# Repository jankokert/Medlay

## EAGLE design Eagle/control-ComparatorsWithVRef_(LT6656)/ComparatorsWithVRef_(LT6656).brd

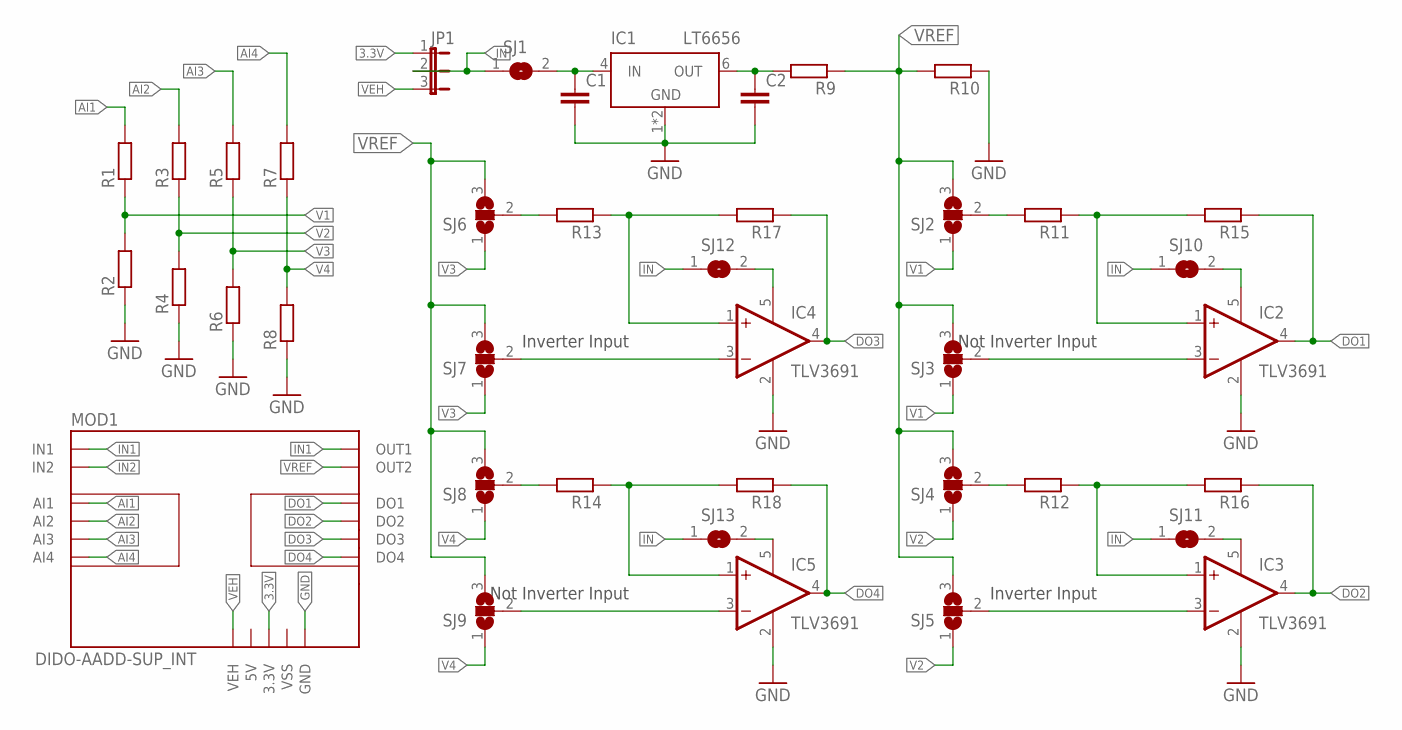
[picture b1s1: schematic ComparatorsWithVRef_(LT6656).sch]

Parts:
C1: 0.1u; C0805
C2: 1u; C0805
IC1: LT6656; TSOT23-6
IC2, IC3, IC4, IC5: TLV3691; DCK
JP1: JP2E; JP2
MOD1: DIDO-AADD-SUP_INT; DIDO-AADD-SUP
R1, R2, R3, R4, R5, R6, R7, R8, R9, R10, R11, R12, R13, R14, R15, R16, R17, R18: R-EU_R0805; R0805
SJ1, SJ10, SJ11, SJ12, SJ13: SJ
SJ2, SJ3, SJ4, SJ5, SJ6, SJ7, SJ8, SJ9: SJ3

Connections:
3.3V: JP1.1, MOD1.3.3V
5V: MOD1.5V
AI1: MOD1.AI1, R1.2
AI2: MOD1.AI2, R3.2
AI3: MOD1.AI3, R5.2
AI4: MOD1.AI4, R7.2
DO1: IC2.4 (OUT), MOD1.DO1, R15.1
DO2: IC3.4 (OUT), MOD1.DO2, R16.1
DO3: IC4.4 (OUT), MOD1.DO3, R17.1
DO4: IC5.4 (OUT), MOD1.DO4, R18.1
GND: C1.2, C2.2, IC1.1 (GND), IC1.2 (GND), IC2.2 (V-), IC3.2 (V-), IC4.2 (V-), IC5.2 (V-), MOD1.GND1 (GND), MOD1.GND2 (GND), MOD1.GND3 (GND), MOD1.GND4 (GND), R2.1, R4.1, R6.1, R8.1, R10.1
IN: JP1.2, SJ1.1, SJ10.1, SJ11.1, SJ12.1, SJ13.1
IN1: MOD1.IN1, MOD1.IN2 (IN1), MOD1.IN3 (IN1), MOD1.IN4 (IN1), MOD1.OUT1, MOD1.OUT2 (OUT1), MOD1.OUT3 (OUT1), MOD1.OUT4 (OUT1)
IN2: MOD1.IN2_1 (IN2), MOD1.IN2_2 (IN2), MOD1.IN2_3 (IN2), MOD1.IN2_4 (IN2)
unnamed: IC3.1 (+IN), R12.1, R16.2
unnamed: IC2.3 (-IN), SJ3.2
unnamed: R12.2, SJ4.2
unnamed: C2.1, IC1.6 (OUT), R9.2
unnamed: IC2.1 (+IN), R11.1, R15.2
unnamed: R11.2, SJ2.2
unnamed: IC3.3 (-IN), SJ5.2
unnamed: R13.2, SJ6.2
unnamed: IC4.3 (-IN), SJ7.2
unnamed: R14.2, SJ8.2
unnamed: IC2.5 (V+), SJ10.2
unnamed: IC4.1 (+IN), R13.1, R17.2
unnamed: IC5.3 (-IN), SJ9.2
unnamed: IC5.1 (+IN), R14.1, R18.2
unnamed: IC5.5 (V+), SJ13.2
unnamed: IC4.5 (V+), SJ12.2
unnamed: IC3.5 (V+), SJ11.2
unnamed: C1.1, IC1.4 (IN), SJ1.2
V1: R1.1, R2.2, SJ2.1, SJ3.1
V2: R3.1, R4.2, SJ4.1, SJ5.1
V3: R5.1, R6.2, SJ6.1, SJ7.1
V4: R7.1, R8.2, SJ8.1, SJ9.1
VEH: JP1.3, MOD1.VEH
VREF: MOD1.OUT2_1 (OUT2), MOD1.OUT2_2 (OUT2), MOD1.OUT2_3 (OUT2), MOD1.OUT2_4 (OUT2), R9.1, R10.2, SJ2.3, SJ3.3, SJ4.3, SJ5.3, SJ6.3, SJ7.3, SJ8.3, SJ9.3
VSS: MOD1.VSS

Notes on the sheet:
Not Inverter Input
Inverter Input

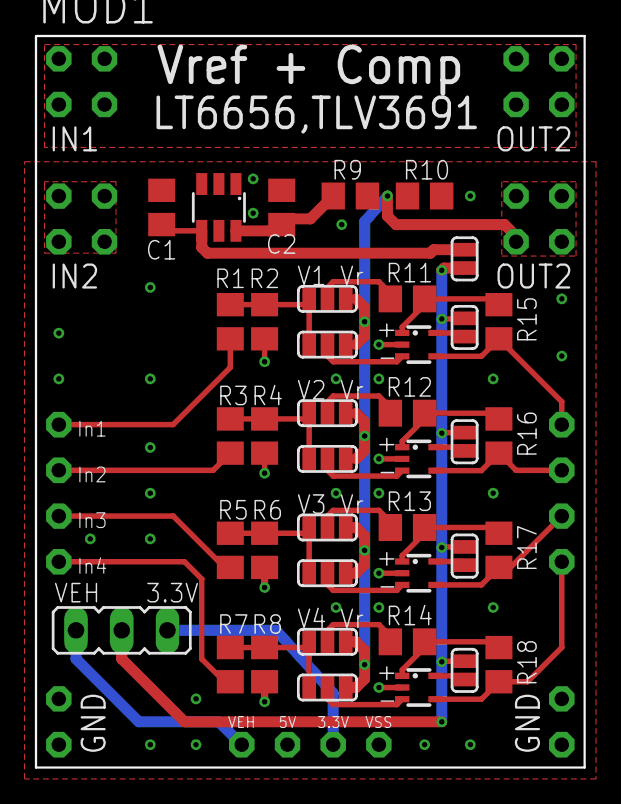
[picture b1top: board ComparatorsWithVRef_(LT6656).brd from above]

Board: 2 copper layers, 30.5 x 40.6 mm, 40 parts (0 on the bottom side), 37 nets.

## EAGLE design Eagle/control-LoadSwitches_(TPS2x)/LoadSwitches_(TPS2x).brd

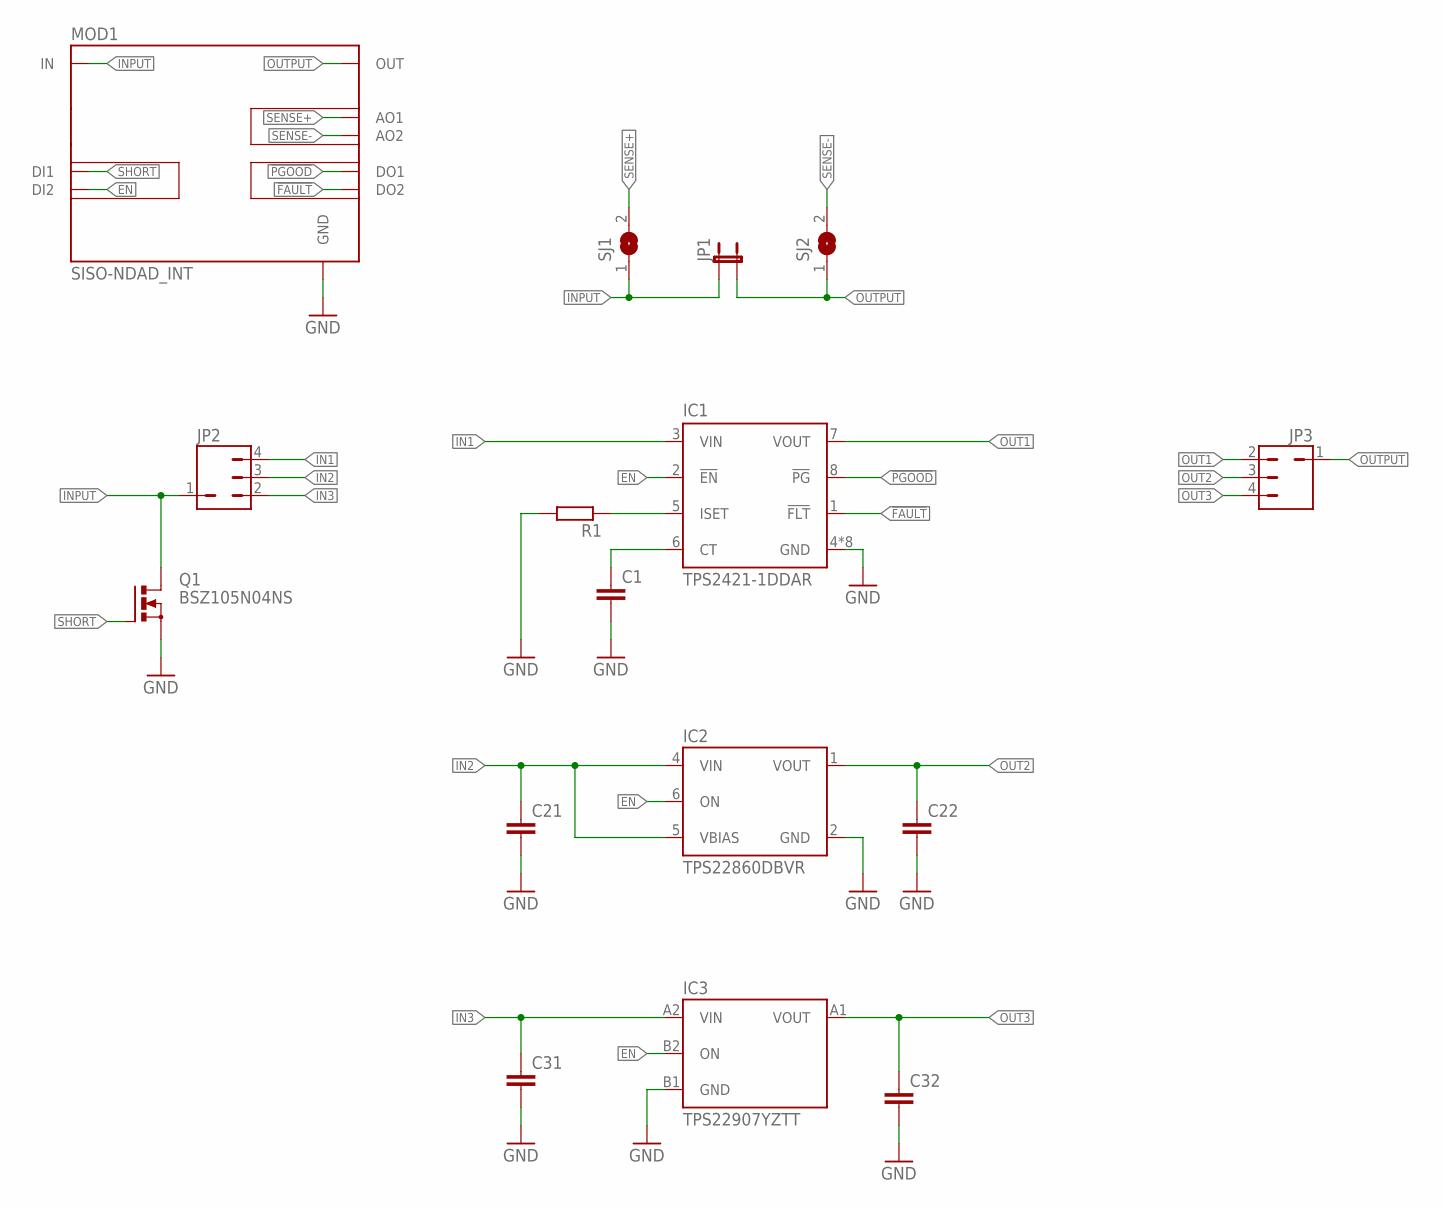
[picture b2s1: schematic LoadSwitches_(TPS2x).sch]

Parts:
C1, C21, C22, C31, C32: C-EUC0805; C0805
IC1: TPS2421-1DDAR; HSOP8
IC2: TPS22860DBVR; SOT23-6
IC3: TPS22907YZTT; BGA4C50P2X2_90X90X63
JP1: JP2_SMALL_PAD
JP2, JP3: JP3Q; JP1-3
MOD1: SISO-NDAD_INT; SISO-NDAD
Q1: BSZ105N04NS; PG-TDSON-8
R1: R-EU_R0805; R0805
SJ1, SJ2: SJ2

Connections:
!FAULT: IC1.1 (!FLT), MOD1.DO2
!PGOOD: IC1.8 (!PG), MOD1.DO1
EN: IC1.2 (!EN), IC2.6 (ON), IC3.B2 (ON), MOD1.DI2
GND: C1.2, C21.2, C22.2, C31.2, C32.2, IC1.4 (GND), IC1.EXP (GND), IC1.P$1 (GND), IC1.P$2 (GND), IC1.P$3 (GND), IC1.P$4 (GND), IC1.P$5 (GND), IC1.P$6 (GND), IC2.2 (GND), IC3.B1 (GND), MOD1.GND1 (GND), MOD1.GND2 (GND), MOD1.GND3 (GND), MOD1.GND4 (GND), Q1.1 (S), Q1.2 (S), Q1.3 (S), R1.2
IN1: IC1.3 (VIN), JP2.4
IN2: C21.1, IC2.4 (VIN), IC2.5 (VBIAS), JP2.3
IN3: C31.1, IC3.A2 (VIN), JP2.2
INPUT: JP1.1, JP2.1, MOD1.IN1 (IN), MOD1.IN2 (IN), MOD1.IN3 (IN), MOD1.IN4 (IN), Q1.5 (D), Q1.6 (D), Q1.7 (D), Q1.8 (D), Q1.TH (D), SJ1.1
unnamed: IC1.5 (ISET), R1.1
unnamed: C1.1, IC1.6 (CT)
OUT1: IC1.7 (VOUT), JP3.2
OUT2: C22.1, IC2.1 (VOUT), JP3.3
OUT3: C32.1, IC3.A1 (VOUT), JP3.4
OUTPUT: JP1.2, JP3.1, MOD1.OUT1_1 (OUT), MOD1.OUT1_2 (OUT), MOD1.OUT1_3 (OUT), MOD1.OUT1_4 (OUT), SJ2.1
SENSE+: MOD1.AO1, SJ1.2
SENSE-: MOD1.AO2, SJ2.2
SHORT: MOD1.DI1, Q1.4 (G)

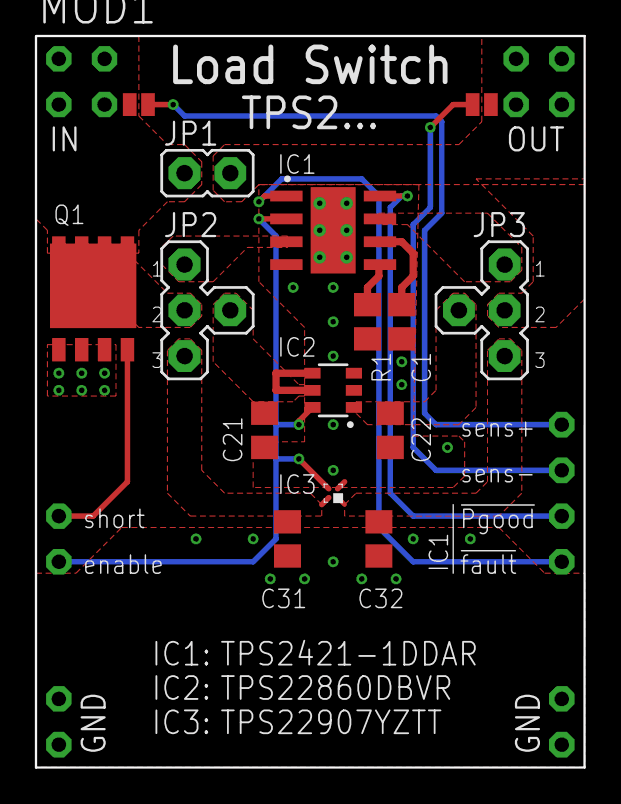
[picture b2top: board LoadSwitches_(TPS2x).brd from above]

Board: 2 copper layers, 30.5 x 40.6 mm, 16 parts (0 on the bottom side), 17 nets.

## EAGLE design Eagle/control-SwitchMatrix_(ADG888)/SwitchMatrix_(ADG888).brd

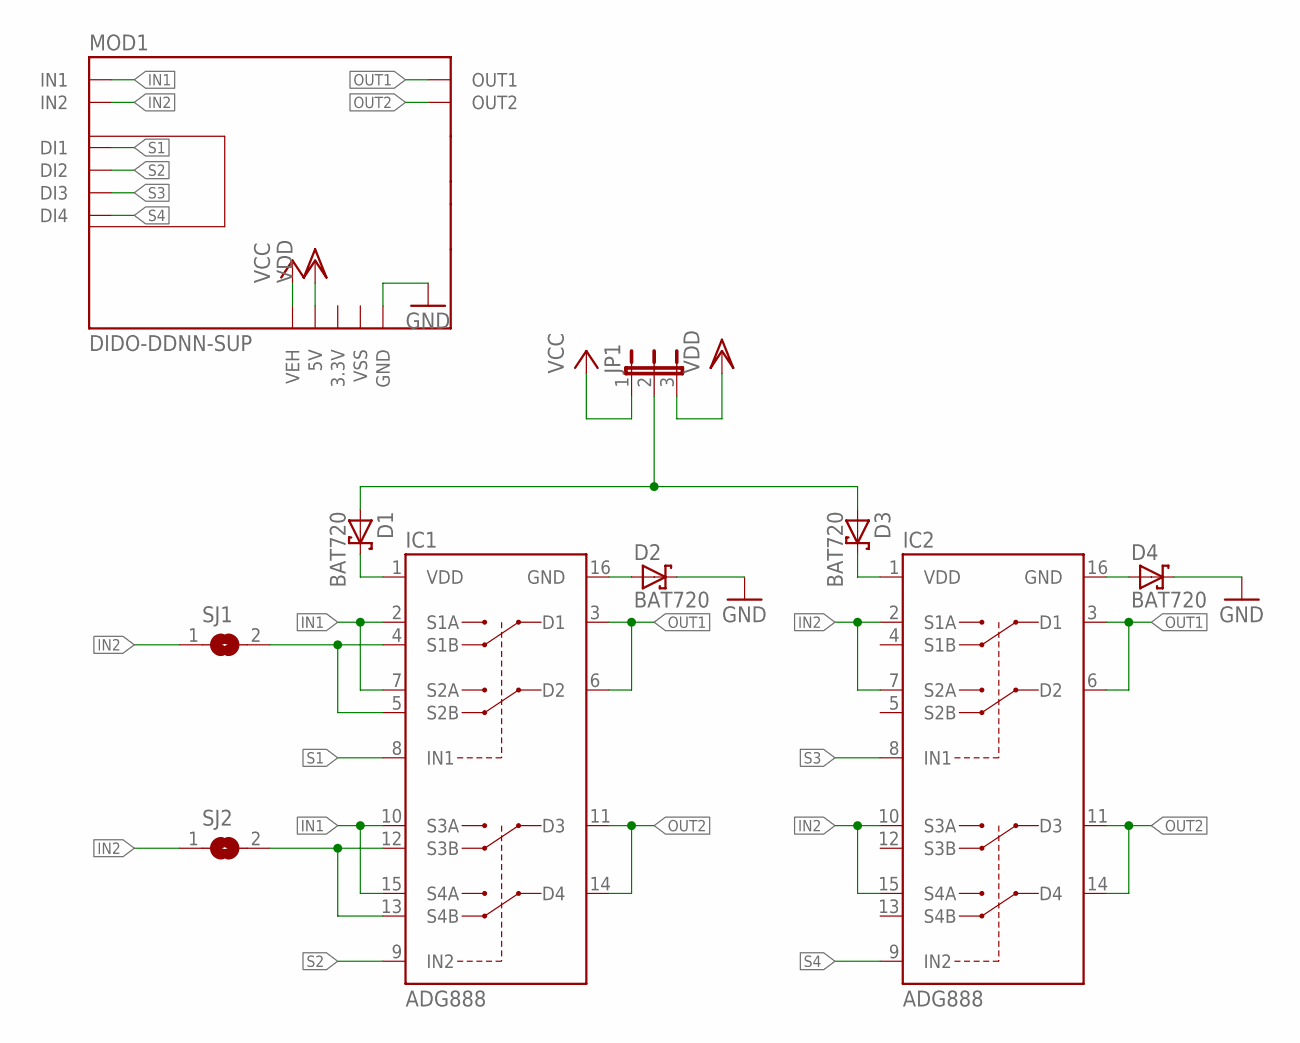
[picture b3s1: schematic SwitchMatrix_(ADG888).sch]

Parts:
D1, D2, D3, D4: BAT720; SOT23
IC1, IC2: ADG888; TSSOP16
JP1: JP2E; JP2
MOD1: DIDO-DDNN-SUP
SJ1, SJ2: SJ

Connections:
3.3V: MOD1.3.3V
GND: D2.3 (C), D4.3 (C), MOD1.GND1 (GND), MOD1.GND2 (GND), MOD1.GND3 (GND), MOD1.GND4 (GND)
IN1: IC1.2 (S1A), IC1.7 (S2A), IC1.10 (S3A), IC1.15 (S4A), MOD1.IN1_1 (IN1), MOD1.IN1_2 (IN1), MOD1.IN1_3 (IN1), MOD1.IN1_4 (IN1)
IN2: IC2.2 (S1A), IC2.7 (S2A), IC2.10 (S3A), IC2.15 (S4A), MOD1.IN2_1 (IN2), MOD1.IN2_2 (IN2), MOD1.IN2_3 (IN2), MOD1.IN2_4 (IN2), SJ1.1, SJ2.1
unnamed: IC1.4 (S1B), IC1.5 (S2B), SJ1.2
unnamed: IC1.12 (S3B), IC1.13 (S4B), SJ2.2
unnamed: D2.1 (A), IC1.16 (GND)
unnamed: D1.3 (C), IC1.1 (VDD)
unnamed: D3.3 (C), IC2.1 (VDD)
unnamed: D4.1 (A), IC2.16 (GND)
unnamed: D1.1 (A), D3.1 (A), JP1.2
OUT1: IC1.3 (D1), IC1.6 (D2), IC2.3 (D1), IC2.6 (D2), MOD1.OUT1_1 (OUT1), MOD1.OUT1_2 (OUT1), MOD1.OUT1_3 (OUT1), MOD1.OUT1_4 (OUT1)
OUT2: IC1.11 (D3), IC1.14 (D4), IC2.11 (D3), IC2.14 (D4), MOD1.OUT2_1 (OUT2), MOD1.OUT2_2 (OUT2), MOD1.OUT2_3 (OUT2), MOD1.OUT2_4 (OUT2)
S1: IC1.8 (IN1), MOD1.DI1
S2: IC1.9 (IN2), MOD1.DI2
S3: IC2.8 (IN1), MOD1.DI3
S4: IC2.9 (IN2), MOD1.DI4
VCC: JP1.1, MOD1.VEH
VDD: JP1.3, MOD1.5V
VSS: MOD1.VSS

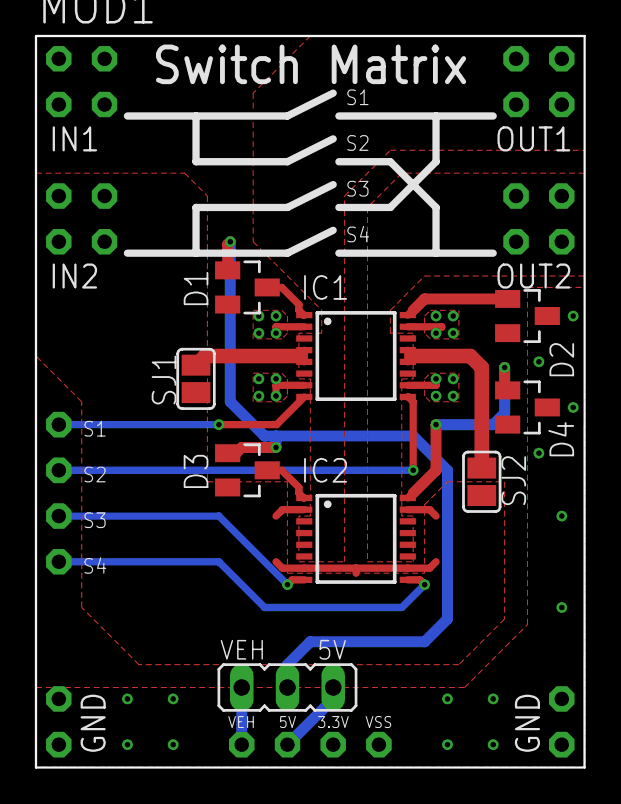
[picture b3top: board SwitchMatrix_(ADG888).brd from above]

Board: 2 copper layers, 30.5 x 40.6 mm, 10 parts (0 on the bottom side), 18 nets.

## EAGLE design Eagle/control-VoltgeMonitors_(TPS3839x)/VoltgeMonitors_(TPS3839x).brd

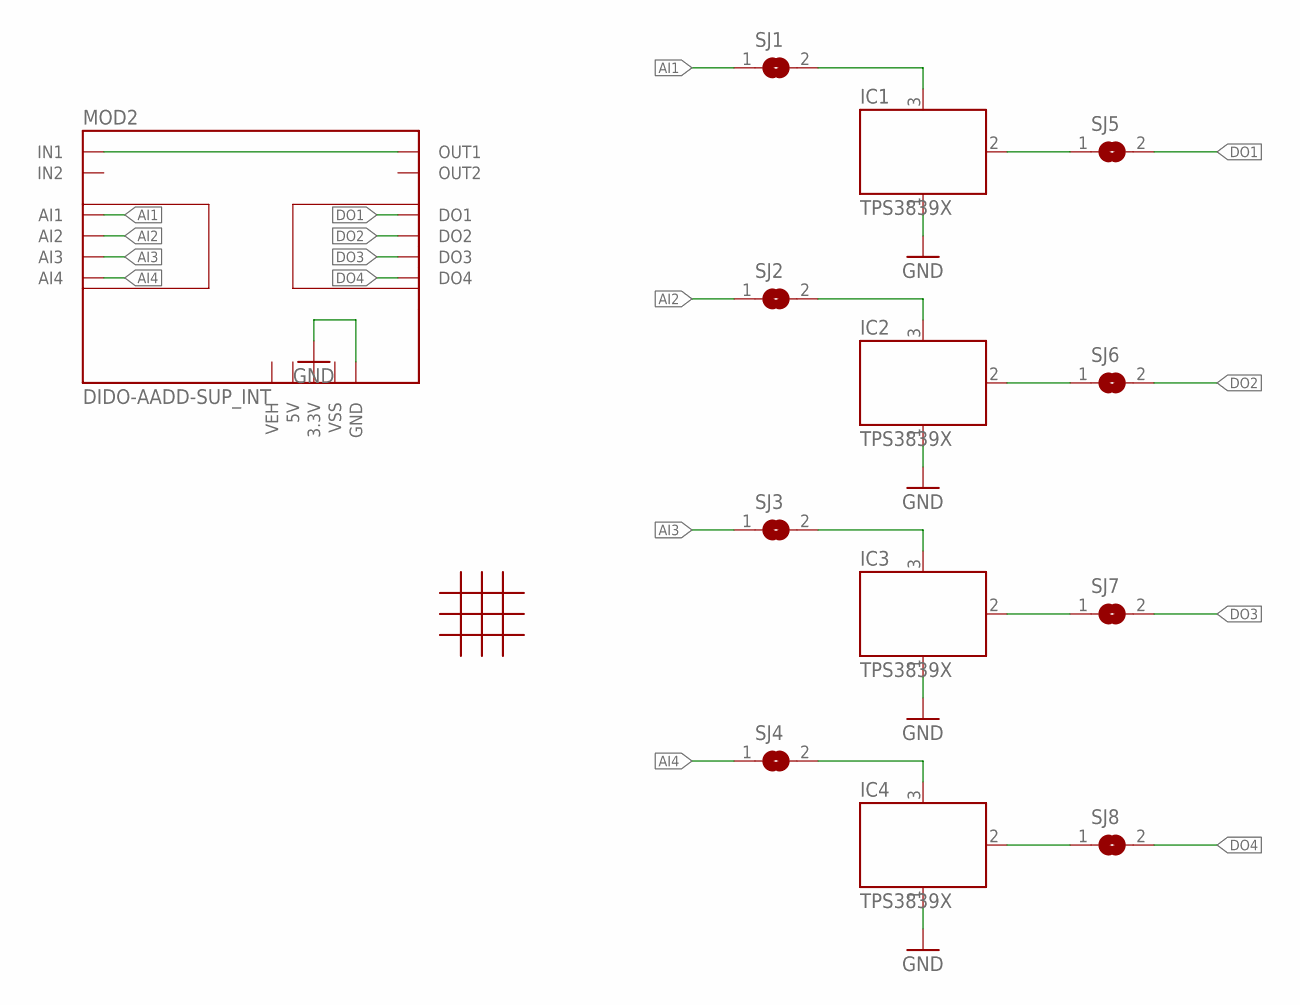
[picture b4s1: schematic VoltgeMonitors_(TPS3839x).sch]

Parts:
IC1, IC2, IC3, IC4: TPS3839X; DBZ_R-PDSO-G3
MOD2: DIDO-AADD-SUP_INT; DIDO-AADD-SUP
SJ1, SJ2, SJ3, SJ4, SJ5, SJ6, SJ7, SJ8: SJ2
U$1: SMD; SMD-PROTOTYPE

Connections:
3.3V: MOD2.3.3V
5V: MOD2.5V
AI1: MOD2.AI1, SJ1.1
AI2: MOD2.AI2, SJ2.1
AI3: MOD2.AI3, SJ3.1
AI4: MOD2.AI4, SJ4.1
DO1: MOD2.DO1, SJ5.2
DO2: MOD2.DO2, SJ6.2
DO3: MOD2.DO3, SJ7.2
DO4: MOD2.DO4, SJ8.2
GND: IC1.1 (GND), IC2.1 (GND), IC3.1 (GND), IC4.1 (GND), MOD2.GND1 (GND), MOD2.GND2 (GND), MOD2.GND3 (GND), MOD2.GND4 (GND)
IN: MOD2.IN1, MOD2.IN2 (IN1), MOD2.IN3 (IN1), MOD2.IN4 (IN1), MOD2.OUT1, MOD2.OUT2 (OUT1), MOD2.OUT3 (OUT1), MOD2.OUT4 (OUT1)
unnamed: IC1.3 (VDD), SJ1.2
unnamed: IC2.3 (VDD), SJ2.2
unnamed: IC3.3 (VDD), SJ3.2
unnamed: IC4.3 (VDD), SJ4.2
unnamed: IC4.2 (/RST), SJ8.1
unnamed: IC3.2 (/RST), SJ7.1
unnamed: IC2.2 (/RST), SJ6.1
unnamed: IC1.2 (/RST), SJ5.1
VEH: MOD2.VEH
VSS: MOD2.VSS

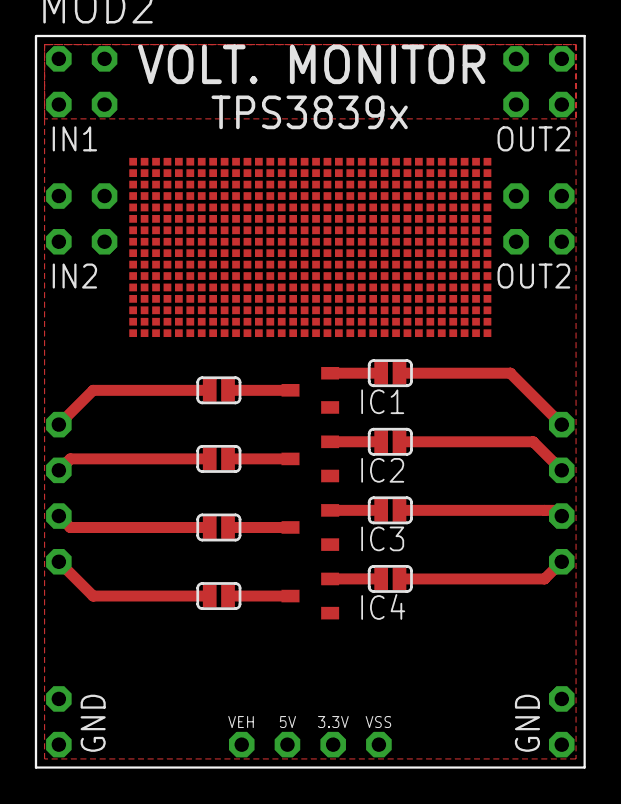
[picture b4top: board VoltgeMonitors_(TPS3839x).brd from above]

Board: 2 copper layers, 30.5 x 40.6 mm, 14 parts (0 on the bottom side), 18 nets.

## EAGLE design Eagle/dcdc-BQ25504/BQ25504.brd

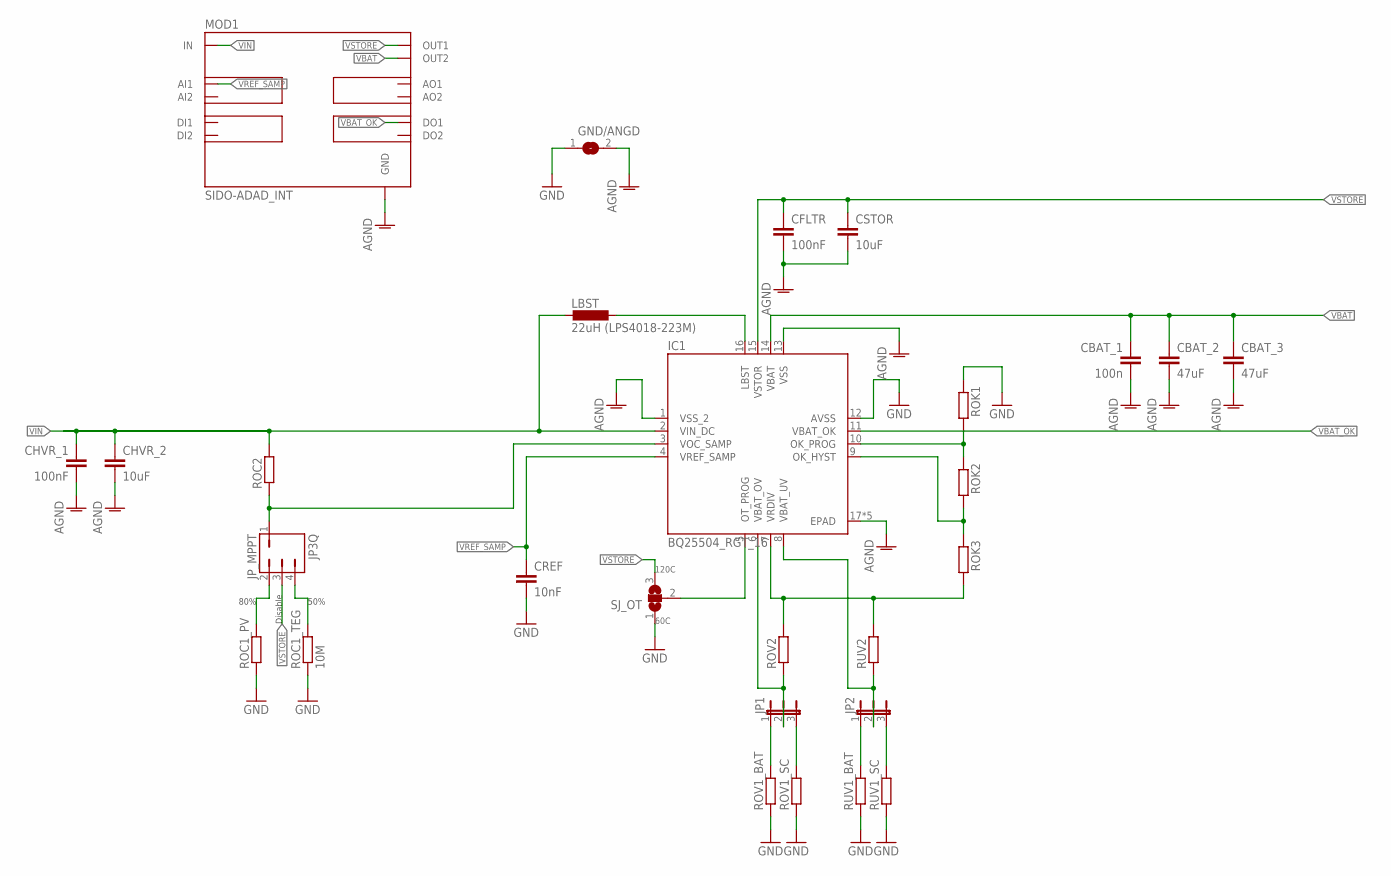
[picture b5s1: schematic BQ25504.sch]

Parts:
CBAT_1: 100n; C0805K
CBAT_2, CBAT_3: 47uF; C0805K
CFLTR: 100nF; C0805K
CHVR_1: 100nF; C0805K
CHVR_2: 10uF; C0805K
CREF: 10nF; C0805K
CSTOR: 10uF; C0805K
GND/ANGD: SJ
IC1: BQ25504_RGT_16; RGT16_1P7X1P7
JP1, JP2: JP2E; JP2
JP_MPPT: JP3Q; JP1-3
LBST: 22uH (LPS4018-223M); LPS4018
MOD1: SIDO-ADAD_INT; SIDO-ADAD
ROC1_PV, ROC2: R-EU_R0805; R0805
ROC1_TEG: 10M; R0805
ROK1, ROK2, ROK3: R-EU_R0805; R0805
ROV1_BAT, ROV1_SC, ROV2: R-EU_R0805; R0805
RUV1_BAT, RUV1_SC, RUV2: R-EU_R0805; R0805
SJ_OT: SJ3

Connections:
AGND: CBAT_1.2, CBAT_2.2, CBAT_3.2, CFLTR.2, CHVR_1.2, CHVR_2.2, CSTOR.2, GND/ANGD.2, IC1.1 (VSS_2), IC1.13 (VSS), IC1.17 (EPAD), IC1.V (EPAD), IC1.V_2 (EPAD), IC1.V_3 (EPAD), IC1.V_4 (EPAD), MOD1.GND1 (GND), MOD1.GND2 (GND), MOD1.GND3 (GND), MOD1.GND4 (GND)
GND: CREF.2, GND/ANGD.1, IC1.12 (AVSS), ROC1_PV.1, ROC1_TEG.1, ROK1.1, ROV1_BAT.1, ROV1_SC.1, RUV1_BAT.1, RUV1_SC.1, SJ_OT.1
unnamed: IC1.16 (LBST), LBST.2
unnamed: JP_MPPT.4, ROC1_TEG.2
unnamed: IC1.10 (OK_PROG), ROK1.2, ROK2.1
unnamed: IC1.9 (OK_HYST), ROK2.2, ROK3.1
unnamed: JP_MPPT.2, ROC1_PV.2
unnamed: IC1.5 (OT_PROG), SJ_OT.2
unnamed: IC1.3 (VOC_SAMP), JP_MPPT.1, ROC2.1
unnamed: JP1.1, ROV1_BAT.2
unnamed: JP1.3, ROV1_SC.2
unnamed: IC1.6 (VBAT_OV), JP1.2, ROV2.1
unnamed: JP2.1, RUV1_BAT.2
unnamed: JP2.3, RUV1_SC.2
unnamed: IC1.8 (VBAT_UV), JP2.2, RUV2.1
VBAT: CBAT_1.1, CBAT_2.1, CBAT_3.1, IC1.14 (VBAT), MOD1.OUT2_1 (OUT2), MOD1.OUT2_2 (OUT2), MOD1.OUT2_3 (OUT2), MOD1.OUT2_4 (OUT2)
VBAT_OK: IC1.11 (VBAT_OK), MOD1.DO1
VIN: CHVR_1.1, CHVR_2.1, IC1.2 (VIN_DC), LBST.1, MOD1.IN1 (IN), MOD1.IN2 (IN), MOD1.IN3 (IN), MOD1.IN4 (IN)
VIN1: IC1.7 (VRDIV), ROK3.2, ROV2.2, RUV2.2
VIN2: ROC2.2
VREF_SAMP: CREF.1, IC1.4 (VREF_SAMP), MOD1.AI1
VSTORE: CFLTR.1, CSTOR.1, IC1.15 (VSTOR), JP_MPPT.3, MOD1.OUT1_1 (OUT1), MOD1.OUT1_2 (OUT1), MOD1.OUT1_3 (OUT1), MOD1.OUT1_4 (OUT1), SJ_OT.3

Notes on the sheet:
120C
60C
80%
50%
Disable

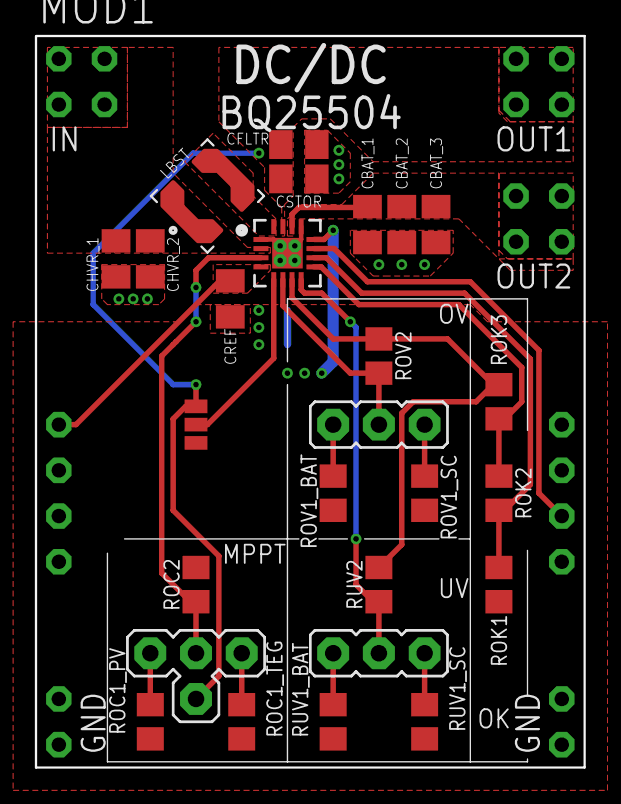
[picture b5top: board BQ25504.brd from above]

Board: 2 copper layers, 30.5 x 40.6 mm, 28 parts (1 on the bottom side), 21 nets.

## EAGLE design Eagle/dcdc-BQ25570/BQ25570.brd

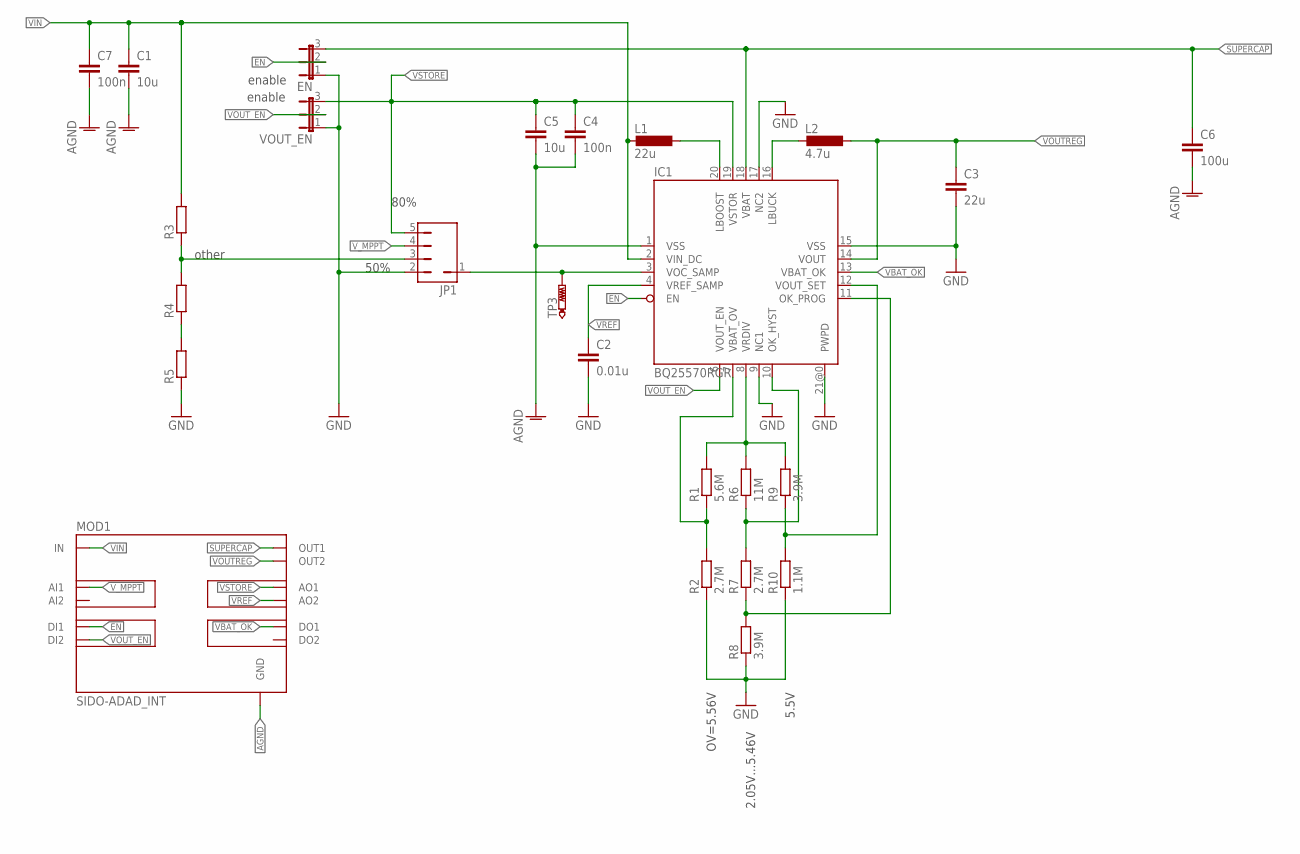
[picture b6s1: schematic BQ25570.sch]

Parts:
C1, C5: 10u; C1206K
C2: 0.01u; C0805K
C3: 22u; C1206K
C4, C7: 100n; C0805K
C6: 100u; C1206K
EN: JP2E; JP2
IC1: BQ25570RGR; QFN20
JP1: JP3Q; JP1-4
L1: 22u; L4035M
L2: 4.7u; L4035M
MOD1: SIDO-ADAD_INT; SIDO-ADAD
R1: 5.6M; R0805
R2, R7: 2.7M; R0805
R3, R4, R5: R-EU_R0805; R0805
R6: 11M; R0805
R8, R9: 3.9M; R0805
R10: 1.1M; R0805
TP3: PTR1B1,27; B1,27
VOUT_EN: JP2E; JP2

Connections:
AGND: C1.2, C4.2, C5.2, C6.2, C7.2, IC1.1 (VSS), MOD1.GND1 (GND), MOD1.GND2 (GND), MOD1.GND3 (GND), MOD1.GND4 (GND)
EN: EN.2, IC1.5 (EN), MOD1.DI1
GND: C2.2, C3.2, EN.1, IC1.9 (NC1), IC1.15 (VSS), IC1.17 (NC2), IC1.21@0 (PWPD), JP1.2, R2.1, R5.1, R8.1, R10.1, VOUT_EN.1
unnamed: JP1.3, R3.1, R4.2
unnamed: IC1.7 (VBAT_OV), R1.1, R2.2
unnamed: IC1.3 (VOC_SAMP), JP1.1, TP3.TP
unnamed: IC1.16 (LBUCK), L2.2
unnamed: IC1.11 (OK_PROG), R7.1, R8.2
unnamed: IC1.10 (OK_HYST), R6.1, R7.2
unnamed: R4.1, R5.2
unnamed: IC1.20 (LBOOST), L1.1
unnamed: IC1.12 (VOUT_SET), R9.1, R10.2
SUPERCAP: C6.1, EN.3, IC1.18 (VBAT), MOD1.OUT1_1 (OUT1), MOD1.OUT1_2 (OUT1), MOD1.OUT1_3 (OUT1), MOD1.OUT1_4 (OUT1)
VBAT_OK: IC1.13 (VBAT_OK), MOD1.DO1
VIN: C1.1, C7.1, IC1.2 (VIN_DC), L1.2, MOD1.IN1 (IN), MOD1.IN2 (IN), MOD1.IN3 (IN), MOD1.IN4 (IN), R3.2
VOUTREG: C3.1, IC1.14 (VOUT), L2.1, MOD1.OUT2_1 (OUT2), MOD1.OUT2_2 (OUT2), MOD1.OUT2_3 (OUT2), MOD1.OUT2_4 (OUT2)
VOUT_EN: IC1.6 (VOUT_EN), MOD1.DI2, VOUT_EN.2
VRDIV: IC1.8 (VRDIV), R1.2, R6.2, R9.2
VREF: C2.1, IC1.4 (VREF_SAMP), MOD1.AO2
VSTORE: C4.1, C5.1, IC1.19 (VSTOR), JP1.5, MOD1.AO1, VOUT_EN.3
V_MPPT: JP1.4, MOD1.AI1

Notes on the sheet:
80%
50%
enable
other
2.05V...5.46V
5.5V
OV=5.56V

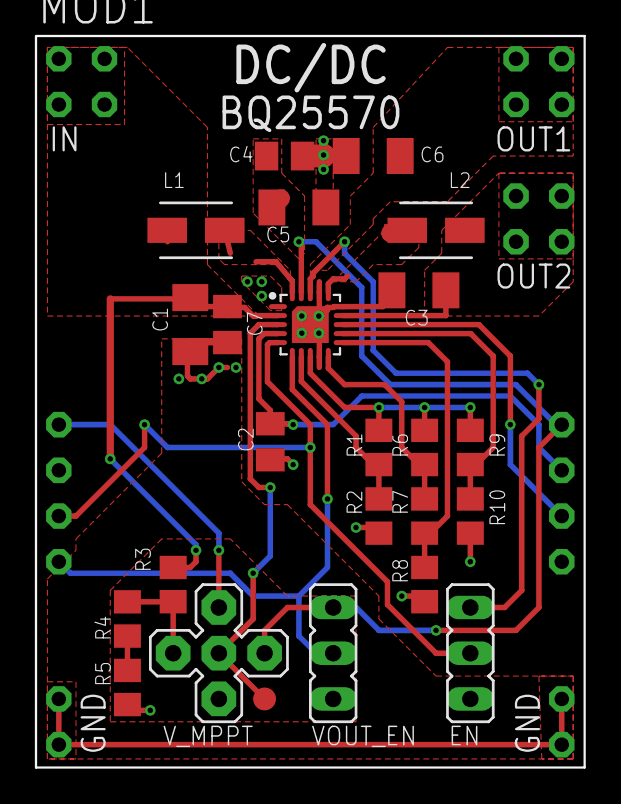
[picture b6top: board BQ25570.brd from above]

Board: 2 copper layers, 30.5 x 40.6 mm, 25 parts (0 on the bottom side), 21 nets.

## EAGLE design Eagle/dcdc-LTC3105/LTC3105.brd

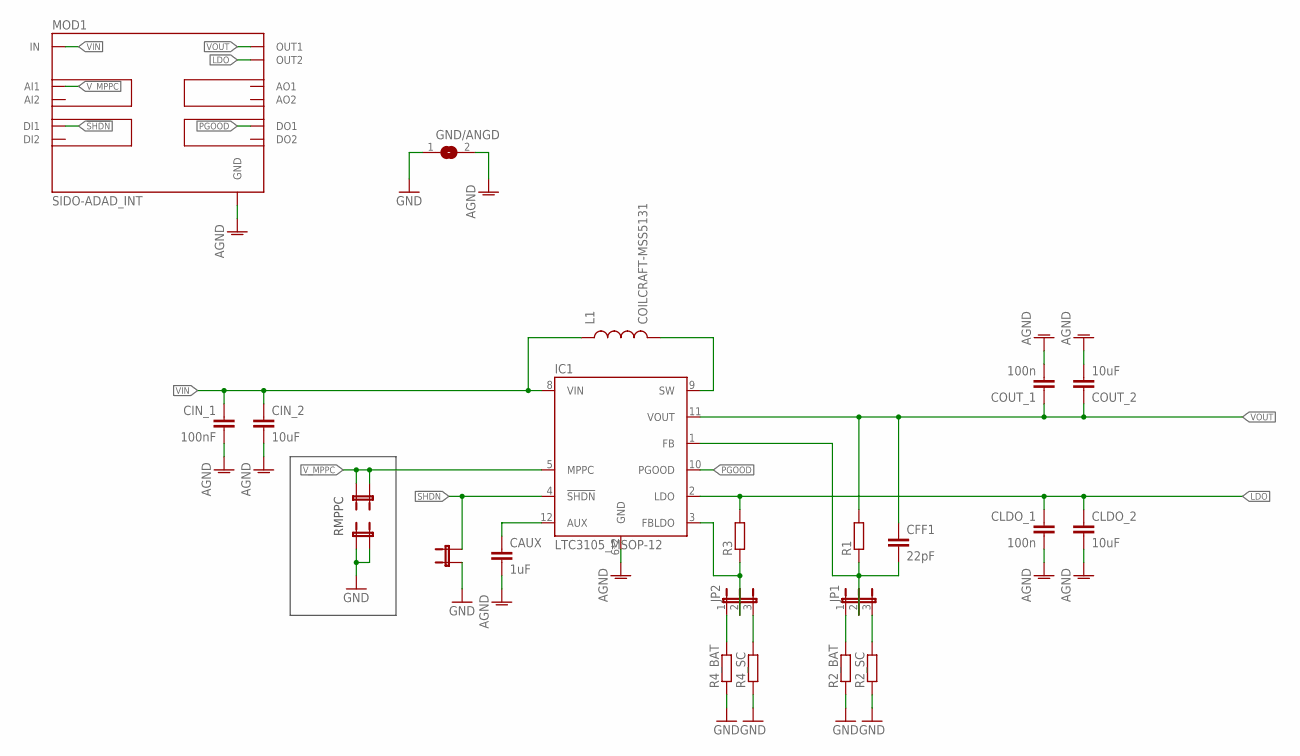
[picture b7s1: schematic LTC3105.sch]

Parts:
CAUX: 1uF; C0805K
CFF1: 22pF; C0805K
CIN_1: 100nF; C0805K
CIN_2: 10uF; C0805K
CLDO_1: 100n; C0805K
CLDO_2: 10uF; C0805K
COUT_1: 100n; C0805K
COUT_2: 10uF; C0805K
GND/ANGD: SJ
IC1: LTC3105_MSOP-12; MSOP-12
JP1, JP2: JP2E; JP2
JP3, JP4, JP5: JP2_SMALL_PAD
L1: COILCRAFT-MSS5131; COILCRAFT_MSS5131
MOD1: SIDO-ADAD_INT; SIDO-ADAD
R1, R2_BAT, R2_SC, R3, R4_BAT, R4_SC: R-EU_R0805; R0805

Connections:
!SHDN: IC1.4 (!SHDN), JP5.2, MOD1.DI1
AGND: CAUX.2, CIN_1.2, CIN_2.2, CLDO_1.2, CLDO_2.2, COUT_1.2, COUT_2.2, GND/ANGD.2, IC1.6 (GND), IC1.7 (GND), MOD1.GND1 (GND), MOD1.GND2 (GND), MOD1.GND3 (GND), MOD1.GND4 (GND)
GND: GND/ANGD.1, JP4.1, JP4.2, JP5.1, R2_BAT.1, R2_SC.1, R4_BAT.1, R4_SC.1
LDO: CLDO_1.1, CLDO_2.1, IC1.2 (LDO), MOD1.OUT2_1 (OUT2), MOD1.OUT2_2 (OUT2), MOD1.OUT2_3 (OUT2), MOD1.OUT2_4 (OUT2), R3.2
unnamed: JP2.1, R4_BAT.2
unnamed: CAUX.1, IC1.12 (AUX)
unnamed: IC1.9 (SW), L1.P$1 (2)
unnamed: JP2.3, R4_SC.2
unnamed: IC1.3 (FBLDO), JP2.2, R3.1
unnamed: JP1.1, R2_BAT.2
unnamed: JP1.3, R2_SC.2
unnamed: CFF1.2, IC1.1 (FB), JP1.2, R1.1
PGOOD: IC1.10 (PGOOD), MOD1.DO1
VIN: CIN_1.1, CIN_2.1, IC1.8 (VIN), L1.P$2 (1), MOD1.IN1 (IN), MOD1.IN2 (IN), MOD1.IN3 (IN), MOD1.IN4 (IN)
VOUT: CFF1.1, COUT_1.1, COUT_2.1, IC1.11 (VOUT), MOD1.OUT1_1 (OUT1), MOD1.OUT1_2 (OUT1), MOD1.OUT1_3 (OUT1), MOD1.OUT1_4 (OUT1), R1.2
V_MPPC: IC1.5 (MPPC), JP3.1, JP3.2, MOD1.AI1

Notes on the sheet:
RMPPC

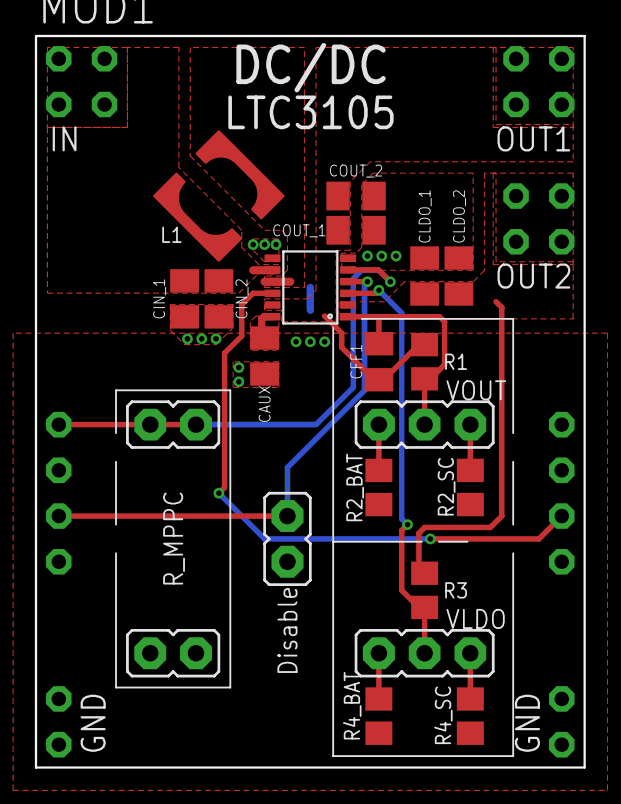
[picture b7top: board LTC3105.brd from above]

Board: 2 copper layers, 30.5 x 40.6 mm, 23 parts (1 on the bottom side), 16 nets.
